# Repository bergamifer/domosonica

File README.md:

# Domosonica - WiFi Audio Streaming Board

## Project Overview

Domosonica is an experimental sound spatialization project that aims to create an accessible platform for the creation and immersive listening of spatialized audio, offering a multidirectional acoustic experience. Unlike traditional approaches that often involve expensive technologies and are confined to exclusive cultural settings, Domosonica takes an inclusive approach by leveraging recycled or low-cost technological resources.

This repository contains the design files for the WiFi-enabled audio streaming board, the core electronic component of the Domosonica project.

## Key Features

- **Inclusive Access**: Designed to break down barriers, making spatialized audio accessible to a wide range of creators, artists, students, and educators.
- **Community Interaction**: Fosters social connections and collaboration between diverse stakeholders in the arts and the local community.
- **Democratizing Sound Art**: By embracing low-cost and recycled technologies, Domosonica democratizes technological sound art, making it available to a broader audience.
- **Cultural Enrichment**: Contributes significantly to the cultural landscape of Parque de Los Patricios, aligning with the identity of the Technology District of Buenos Aires.

## Technical Specifications

### Hardware Components

1. **ESP32 Microcontroller**: A powerful microcontroller with Wi-Fi and Bluetooth capabilities, serving as the heart of the project. It handles internet connectivity, file storage, and audio output.

2. **TDA7496 Stereo Amplifier**: Each board includes a stereo amplifier capable of driving a pair of speakers directly.

3. **SPIFFS (Serial Peripheral Interface Flash File System)**: An onboard file system used by the ESP32 for storing files, useful for caching audio content.

4. **I2S Digital Audio Interface**: A communication protocol specifically designed for digital audio. The ESP32's I2S interface connects to the internal DAC for audio output.

5. **Recycled Speakers**: The system uses speakers salvaged from old televisions, mounted in custom 3D-printed enclosures.

### Circuitry

- **I2S Pins**: The ESP32 is connected to the DAC using specific pins dedicated to I2S communication. These pins transmit the clock signals and the audio data.
- **Power Supply**: The ESP32 and the audio output devices require a stable power supply. USB power or a regulated power adapter can be used.
- **Stereo Output**: Each board drives two speakers independently for stereo sound reproduction.

### Software Components

- **WiFi Library**: For connecting the ESP32 to the internet via Wi-Fi.
- **HTTPClient Library**: For handling HTTP requests to download audio files.
- **SPIFFS Library**: For interfacing with the ESP32's onboard file system.
- **AudioTools Library**: A comprehensive library for audio playback, including support for various audio formats and protocols, including MP3 decoding and I2S.
- **AudioLibs and AudioCodecs**: Additional libraries that provide specific functionality, such as interfacing with the SPIFFS and decoding audio files.

### Setup and Configuration

- Wi-Fi credentials and target URL for audio streams are specified in the firmware.
- I2S and audio playback settings are configured to match the capabilities of the ESP32 and the connected audio hardware.

### Usage

Once the system is powered and the firmware is running:
1. The ESP32 connects to the specified Wi-Fi network.
2. It receives audio streams from the network.
3. Audio playback occurs automatically using the I2S protocol through the TDA7496 amplifier.

## The Dome Installation

The geodesic dome measures 4 meters in diameter and is suspended from the ceiling of "Circo" at CheLA. The structure is held by 5 attachment points (carabiners), keeping the space below free for visitors to explore its interior from a sonic perspective.

### Speaker Design

30 custom enclosures were designed and 3D printed, each housing a recycled television speaker. These speakers were mounted at the nodes of the geodesic dome structure and connected in pairs to each streaming board.

### Board Manufacturing

The PCB was designed from scratch using KiCad (open-source software). The boards were manufactured in China and then hand-soldered at the Pedalúdico workshop at CheLA.

## Location

**CheLA (Centro Hipermediático Experimental Latinoamericano)** is a cultural center located in Buenos Aires, Argentina. It is known for its focus on experimental and multimedia arts, technology, and cultural activities. CheLA provides a space for artists, creators, and researchers to explore various forms of art and technology.

## Educational Workshops

The project included a series of workshops:

- **Amplifier Building Workshops**: A series of 3 workshops (15 participants each) where young people built amplifiers using recycled TV speakers. Participants took home their own amplifiers to connect to their phones and listen to music.

- **FADU (UBA) Collaborations**: Practical sessions were conducted with design students from the Faculty of Architecture, Design and Urbanism at the University of Buenos Aires.

- **Community Building**: Neighborhood residents from Barracas participated in the construction of the dome, which was assembled using PVC pipes shaped with a heat gun.

## Final Conclusions

### Technical Learnings

The ESP32 microcontroller, while powerful and cost-effective, proved to have limitations when processing large volumes of audio signals simultaneously. The board was designed with only **two stereo channels** per unit, which initially seemed limiting for an immersive audio installation.

### Scaling the Solution

To overcome the channel limitation, we manufactured **20 boards in total**, resulting in **40 independent audio channels** distributed throughout the dome. While achieving perfect synchronization across all WiFi-connected units presented challenges, we managed to obtain sufficient synchronization to create compelling surround sound effects.

### Artistic Results

The system enabled some truly **interesting surround sound experiments** inside the dome. The ability to independently control each speaker pair over the local network opened creative possibilities for spatial audio compositions and performances.

### Future Potential

The dome has significant untapped potential. Our vision is to develop a platform that would allow artists from around the world to simultaneously stream their instruments to each speaker independently, creating a new paradigm for collaborative spatial audio performances.

## Safety Notes

- Ensure the power supply is within the acceptable range for the ESP32 and other components to avoid damage.
- Be cautious with speaker volume to prevent hearing damage.
- Properly insulate all connections to prevent shorts.

## License

Domosonica is an open source project. Feel free to use, modify, and share it within the terms of the license.

## Contributing

We welcome contributions from artists, technologists, educators, and anyone interested in pushing the boundaries of sound art.

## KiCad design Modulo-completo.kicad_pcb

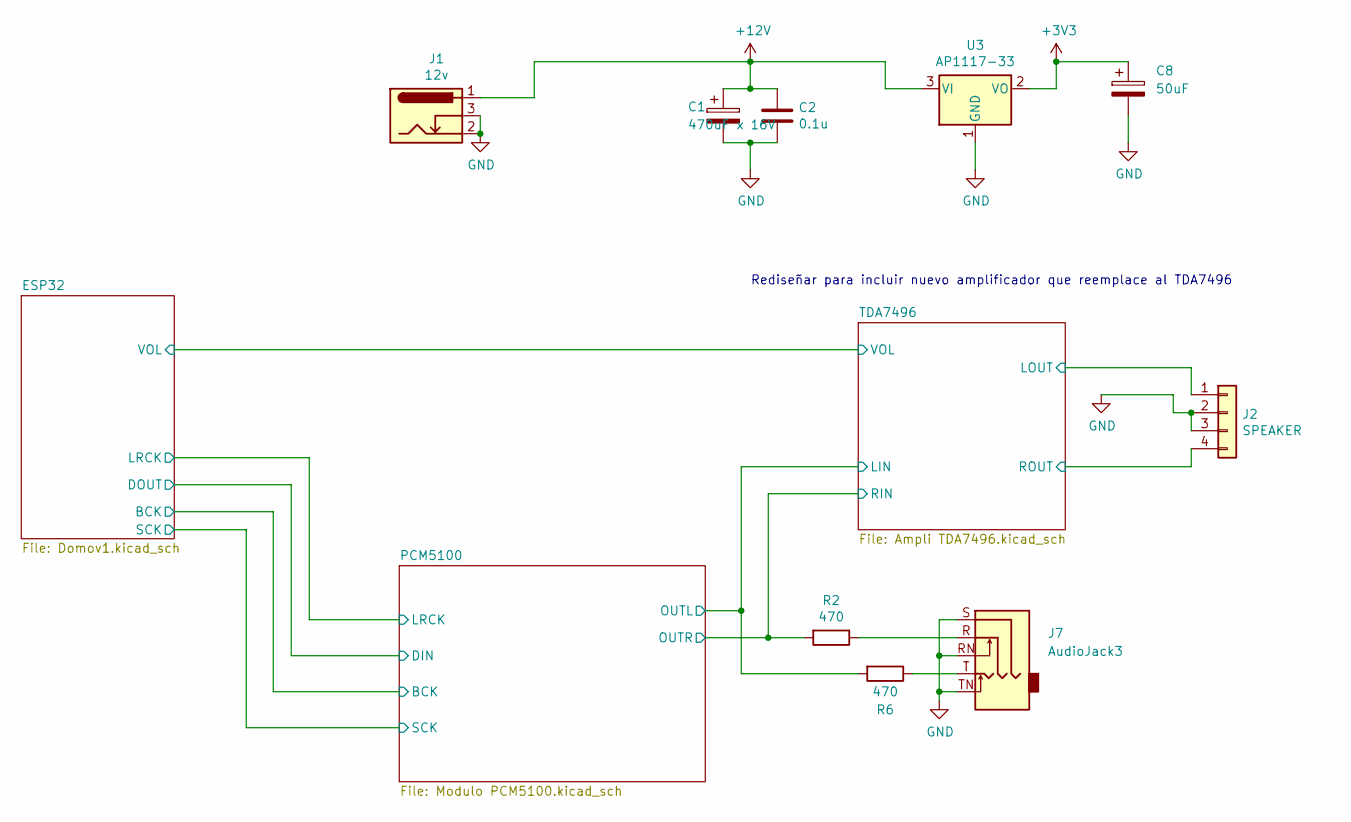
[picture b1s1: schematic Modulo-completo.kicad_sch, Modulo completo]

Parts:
C1: 470uF x 16V; C_Radial_D8.0mm_H11.5mm_P3.50mm
C2: 0.1u; C_0805_2012Metric_Pad1.18x1.45mm_HandSolder
C8: 50uF; C_Radial_D5.0mm_H11.0mm_P2.00mm
J1: 12v; BarrelJack_CUI_PJ-102AH_Horizontal
J2: SPEAKER; JST_XH_B4B-XH-A_1x04_P2.50mm_Vertical
J7: AudioJack3; Jack_3.5mm_Tayda
R2, R6: 470; R_Axial_DIN0207_L6.3mm_D2.5mm_P7.62mm_Horizontal
U3: AP1117-33; SOT-223-3_TabPin2

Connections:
+3V3: C8.1, U3.2 (VO); also elsewhere on the board
+12V: C1.1, C2.1, J1.1, U3.3 (VI); also elsewhere on the board
/PCM5100/OUTL: R6.2; also elsewhere on the board
/PCM5100/OUTR: R2.2; also elsewhere on the board
/TDA7496/LOUT: J2.1; also elsewhere on the board
/TDA7496/ROUT: J2.4; also elsewhere on the board
GND: C1.2, C2.2, C8.2, J1.2, J1.3, J2.2, J2.3, J7.RN, J7.S, J7.TN, U3.1 (GND); also elsewhere on the board
unnamed: J7.R, R2.1
unnamed: J7.T, R6.1

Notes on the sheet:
Rediseñar para incluir nuevo amplificador que reemplace al TDA7496

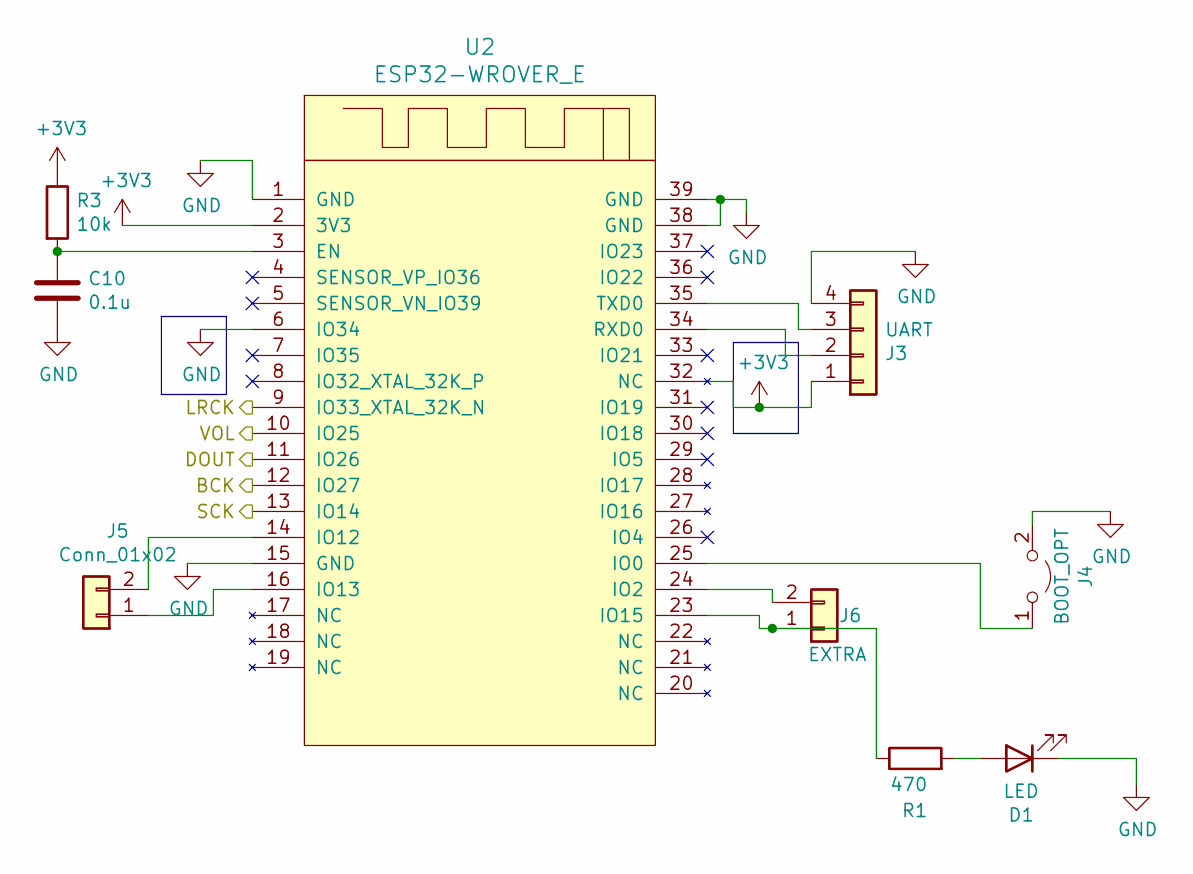
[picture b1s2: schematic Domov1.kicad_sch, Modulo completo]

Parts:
C10: 0.1u; C_0805_2012Metric_Pad1.18x1.45mm_HandSolder
D1: LED; LED_D3.0mm
J3: UART; PinHeader_1x04_P2.54mm_Vertical
J4: BOOT_OPT; PinHeader_1x02_P2.54mm_Vertical
J5: Conn_01x02; PinHeader_1x02_P2.54mm_Vertical
J6: EXTRA; PinHeader_1x02_P2.54mm_Vertical
R1: 470; R_Axial_DIN0207_L6.3mm_D2.5mm_P7.62mm_Horizontal
R3: 10k; R_Axial_DIN0207_L6.3mm_D2.5mm_P7.62mm_Horizontal
U2: ESP32-WROVER_E; ESP32-WROVER(EDIT)

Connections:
+3V3: J3.1, R3.1, U2.2 (3V3), U2.32 (NC); also elsewhere on the board
/ESP32/BCK: U2.12 (IO27); also elsewhere on the board
/ESP32/DOUT: U2.11 (IO26); also elsewhere on the board
/ESP32/LRCK: U2.9 (IO33_XTAL_32K_N); also elsewhere on the board
/ESP32/SCK: U2.13 (IO14); also elsewhere on the board
/ESP32/VOL: U2.10 (IO25); also elsewhere on the board
GND: C10.2, D1.1 (K), J3.4, J4.2 (B), U2.1 (GND), U2.6 (IO34), U2.15 (GND), U2.38 (GND), U2.39 (GND); also elsewhere on the board
unnamed: C10.1, R3.2, U2.3 (EN)
unnamed: D1.2 (A), R1.2
unnamed: J3.2, U2.34 (RXD0)
unnamed: J3.3, U2.35 (TXD0)
unnamed: J4.1 (A), U2.25 (IO0)
unnamed: J5.1, U2.16 (IO13)
unnamed: J5.2, U2.14 (IO12)
unnamed: J6.1, R1.1, U2.23 (IO15)
unnamed: J6.2, U2.24 (IO2)

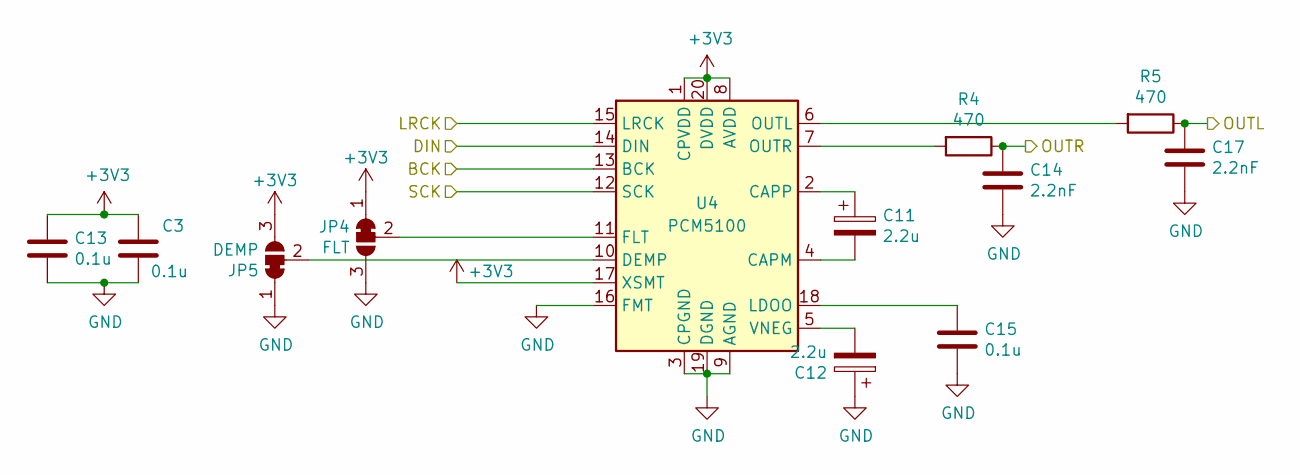
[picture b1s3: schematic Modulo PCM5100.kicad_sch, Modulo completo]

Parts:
C3, C13, C15: 0.1u; C_0805_2012Metric_Pad1.18x1.45mm_HandSolder
C11, C12: 2.2u; C_Radial_D5.0mm_H11.0mm_P2.00mm
C14, C17: 2.2nF; C_Rect_L7.0mm_W2.5mm_P5.00mm
JP4: FLT; SolderJumper-3_P1.3mm_Bridged12_RoundedPad1.0x1.5mm
JP5: DEMP; SolderJumper-3_P1.3mm_Bridged12_RoundedPad1.0x1.5mm
R4, R5: 470; R_Axial_DIN0207_L6.3mm_D2.5mm_P7.62mm_Horizontal
U4: PCM5100; TSSOP-20_4.4x6.5mm_P0.65mm

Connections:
+3V3: C3.1, C13.1, JP4.1 (A), JP5.3 (B), U4.1 (CPVDD), U4.8 (AVDD), U4.17 (XSMT), U4.20 (DVDD); also elsewhere on the board
/ESP32/BCK: U4.13 (BCK); also elsewhere on the board
/ESP32/DOUT: U4.14 (DIN); also elsewhere on the board
/ESP32/LRCK: U4.15 (LRCK); also elsewhere on the board
/ESP32/SCK: U4.12 (SCK); also elsewhere on the board
/PCM5100/OUTL: C17.1, R5.1; also elsewhere on the board
/PCM5100/OUTR: C14.1, R4.1; also elsewhere on the board
GND: C3.2, C12.1, C13.2, C14.2, C15.2, C17.2, JP4.3 (B), JP5.1 (A), U4.3 (CPGND), U4.9 (AGND), U4.16 (FMT), U4.19 (DGND); also elsewhere on the board
unnamed: C11.1, U4.2 (CAPP)
unnamed: C11.2, U4.4 (CAPM)
unnamed: C12.2, U4.5 (VNEG)
unnamed: C15.1, U4.18 (LDOO)
unnamed: JP4.2 (C), U4.11 (FLT)
unnamed: JP5.2 (C), U4.10 (DEMP)
unnamed: R4.2, U4.7 (OUTR)
unnamed: R5.2, U4.6 (OUTL)

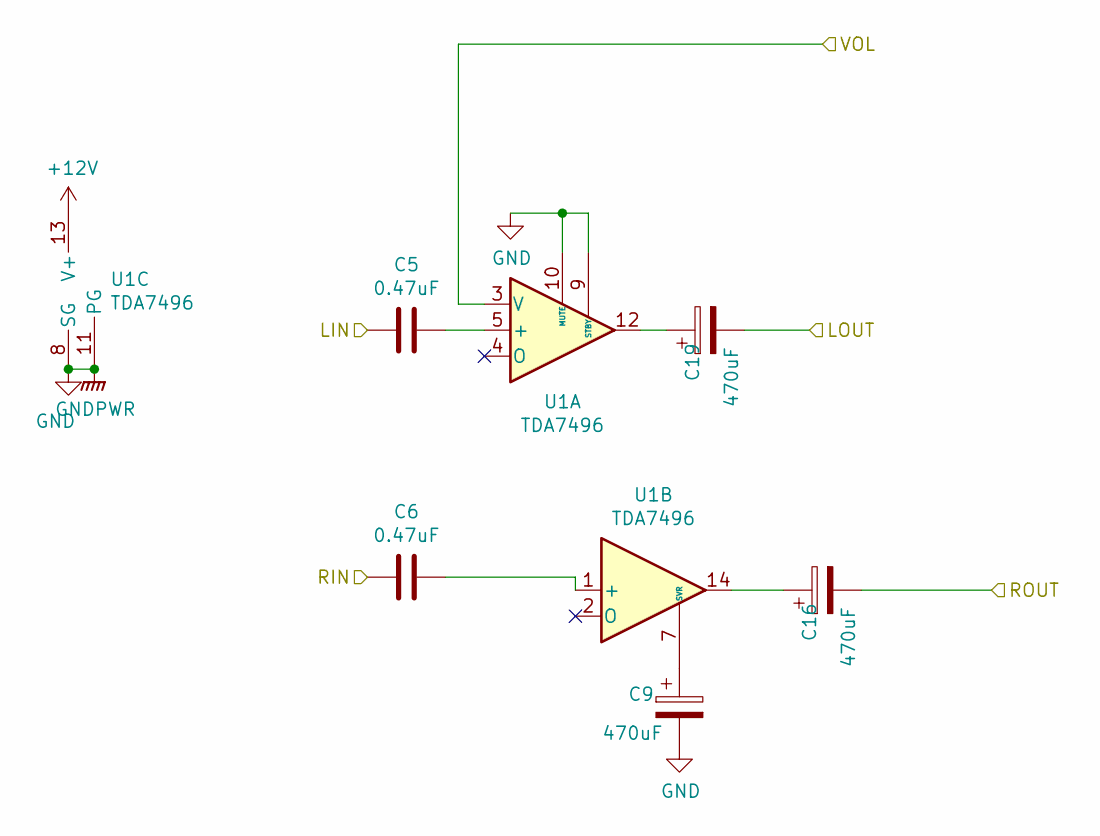
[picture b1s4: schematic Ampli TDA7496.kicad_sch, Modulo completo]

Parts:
C5, C6: 0.47uF; C_Disc_D4.3mm_W1.9mm_P5.00mm
C9, C16, C19: 470uF; C_Radial_D8.0mm_H11.5mm_P3.50mm
U1: TDA7496; TO-220-15_P2.54x2.54mm_StaggerOdd_Lead4.58mm_Vertical

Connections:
+12V: U1.13 (V+); also elsewhere on the board
/ESP32/VOL: U1.3 (V); also elsewhere on the board
/PCM5100/OUTL: C5.2; also elsewhere on the board
/PCM5100/OUTR: C6.2; also elsewhere on the board
/TDA7496/LOUT: C19.2; also elsewhere on the board
/TDA7496/ROUT: C16.2; also elsewhere on the board
GND: C9.2, U1.8 (SG), U1.9 (STBY), U1.10 (MUTE), U1.11 (PG), U1.15 (PG); also elsewhere on the board
unnamed: C5.1, U1.5 (+)
unnamed: C6.1, U1.1 (+)
unnamed: C9.1, U1.7 (SVR)
unnamed: C16.1, U1.14
unnamed: C19.1, U1.12

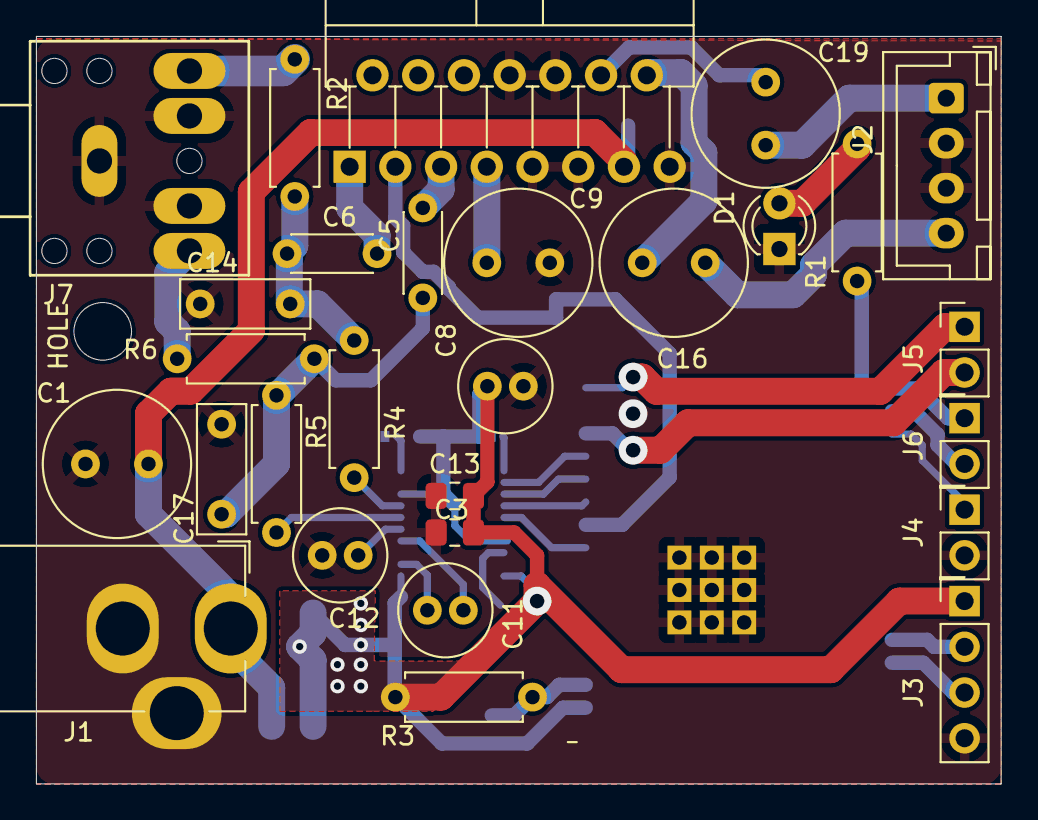
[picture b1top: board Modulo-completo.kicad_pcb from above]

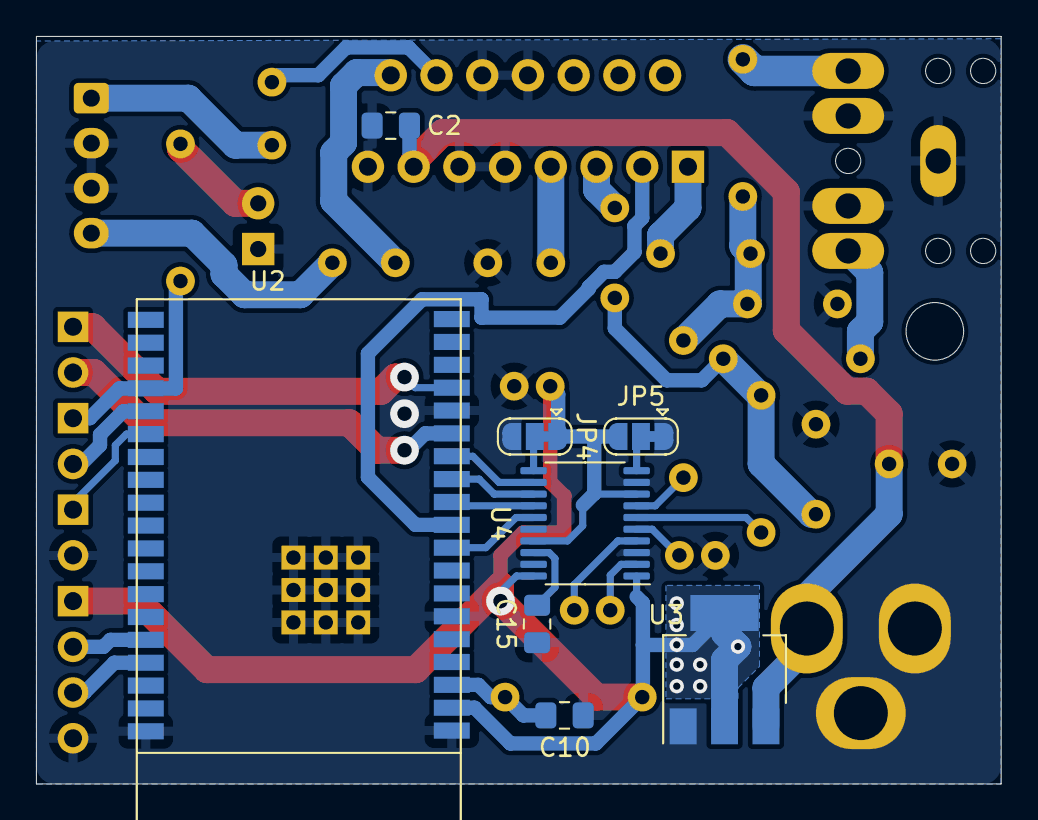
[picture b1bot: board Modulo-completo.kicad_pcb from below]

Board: 2 copper layers, 53.6 x 41.5 mm, 37 parts (8 on the bottom side), 36 nets.

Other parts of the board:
HOLE: MH; MountingHole_3.2mm_M3

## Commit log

2023-11-05 Create Readme-electronics
2023-11-05 Rename Readme-electronics to README.md
2026-01-25 Version final
2026-01-25 Add .gitignore file for KiCad project
2026-01-25 Remove obsolete Gerber files and schematics; add new PNG render of the project.
2026-02-04 Agregué renders y plots
